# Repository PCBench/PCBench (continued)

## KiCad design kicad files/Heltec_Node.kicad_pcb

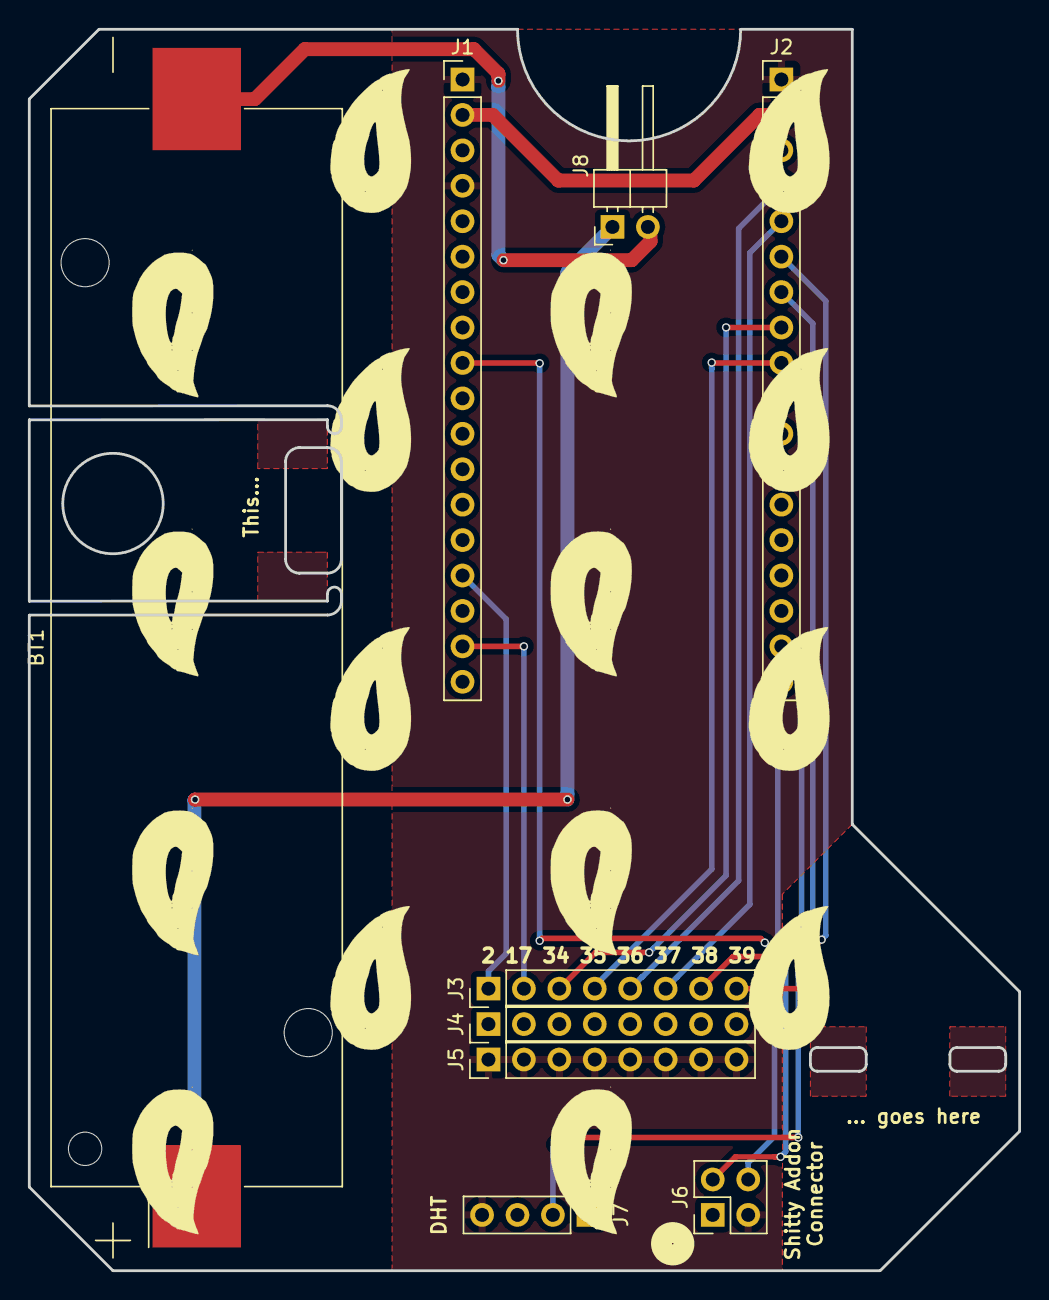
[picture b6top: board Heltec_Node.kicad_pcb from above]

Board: 2 copper layers, 71.0 x 89.0 mm, 9 parts (0 on the bottom side), 16 nets.

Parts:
BT1: Battery_Cell; Keystone_1042_1x18650
J1, J2: Conn_01x18_Female; Socket_Strip_Straight_1x18_Pitch2.54mm
J3, J4, J5: Conn_01x08; Pin_Header_Straight_1x08_Pitch2.54mm
J6: Conn_02x02_Top_Bottom; Pin_Header_Straight_2x02_Pitch2.54mm
J7: Conn_01x04; Pin_Header_Straight_1x04_Pitch2.54mm
J8: Conn_01x02; Pin_Header_Angled_1x02_Pitch2.54mm

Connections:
2: J1.15, J3.1
17: J1.17, J3.2
34: J2.8, J3.3
35: J2.9, J3.4
36: J2.4, J3.5
37: J2.5, J3.6
38: J2.6, J3.7
39: J2.7, J3.8
+3V3: J1.3, J2.3, J4.1, J4.2, J4.3, J4.4, J4.5, J4.6, J4.7, J4.8, J6.1, J7.1
+5V: J1.2, J2.2
DHT_D: J2.17, J7.2
GND: J1.1, J1.4, J2.1, J5.1, J5.2, J5.3, J5.4, J5.5, J5.6, J5.7, J5.8, J6.3, J7.4
unnamed: BT1.1, J8.1
unnamed: BT1.2, J8.2
SCL: J1.9, J6.4
SDA: J2.18, J6.2

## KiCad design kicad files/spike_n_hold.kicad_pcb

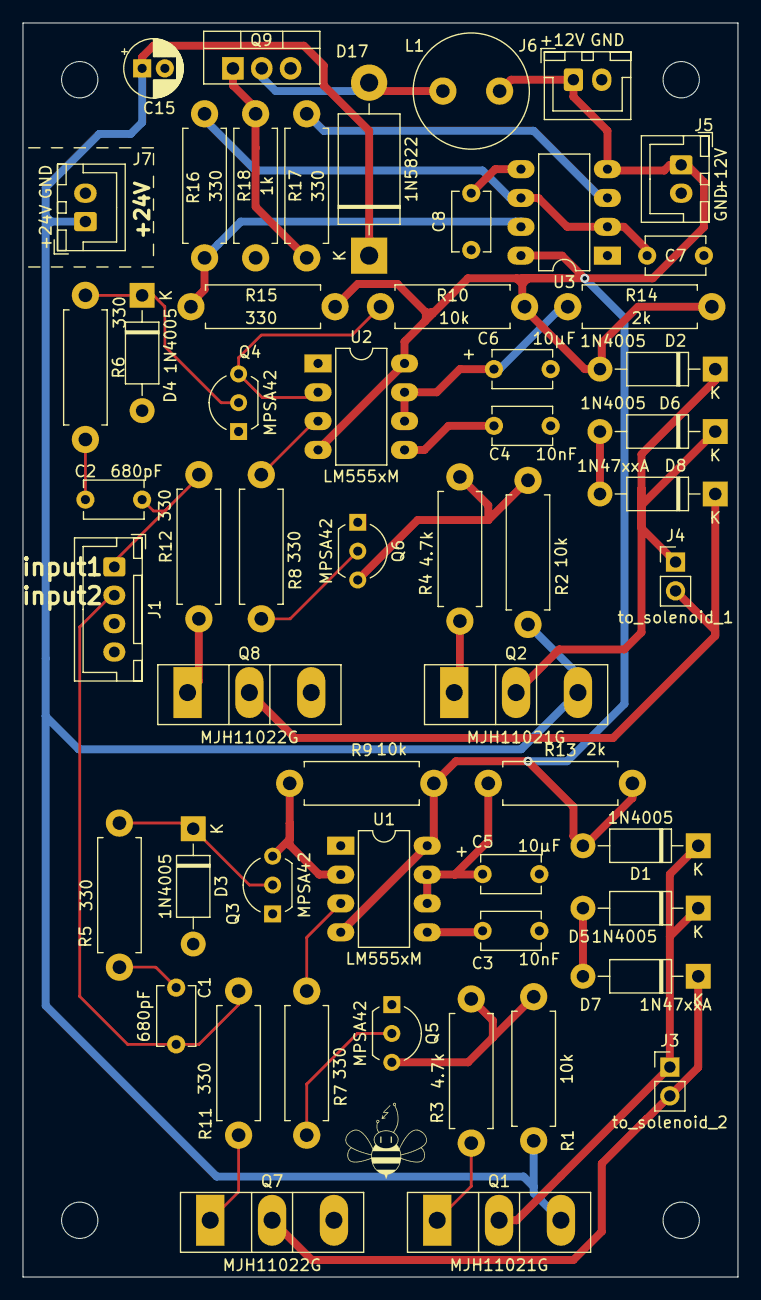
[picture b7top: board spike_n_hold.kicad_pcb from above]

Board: 2 copper layers, 63.0 x 110.5 mm, 59 parts (0 on the bottom side), 37 nets.

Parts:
C1, C2: 680pF; C_Disc_D5.1mm_W3.2mm_P5.00mm
C3, C4, C7, C8: 10nF; C_Disc_D5.1mm_W3.2mm_P5.00mm
C5, C6: 10µF; C_Disc_D5.1mm_W3.2mm_P5.00mm
C15: 22µF; CP_Radial_D5.0mm_P2.00mm
D1, D2, D3, D4, D5, D6: 1N4005; D_DO-41_SOD81_P10.16mm_Horizontal
D7, D8: 1N47xxA; D_DO-41_SOD81_P10.16mm_Horizontal
D17: 1N5822; D_DO-201AD_P15.24mm_Horizontal
H1, H2, H3, H4: MountingHole; MountingHole_3.2mm_M3
J1: Conn_01x04_Female; JST_XH_B4B-XH-A_1x04_P2.50mm_Vertical
J3: to_solenoid_2; PinHeader_1x02_P2.54mm_Vertical
J4: to_solenoid_1; PinHeader_1x02_P2.54mm_Vertical
J5, J6, J7: Conn_01x02; JST_XH_B2B-XH-A_1x02_P2.50mm_Vertical
L1: 33µH; L_Radial_D10.0mm_P5.00mm_Neosid_SD12_style3
Q1, Q2: MJH11021G; TO-247-3_Vertical
Q3, Q4, Q5, Q6: MPSA42; TO-92L_Inline_Wide
Q7, Q8: MJH11022G; TO-247-3_Vertical
Q9: IRFZ24NPBF; TO-220-3_Vertical
R1, R2, R9, R10: 10k; R_Axial_DIN0411_L9.9mm_D3.6mm_P12.70mm_Horizontal
R3, R4: 4.7k; R_Axial_DIN0411_L9.9mm_D3.6mm_P12.70mm_Horizontal
R5, R6, R7, R8, R11, R12, R15, R16, R17: 330; R_Axial_DIN0411_L9.9mm_D3.6mm_P12.70mm_Horizontal
R13, R14: 2k; R_Axial_DIN0411_L9.9mm_D3.6mm_P12.70mm_Horizontal
R18: 1k; R_Axial_DIN0411_L9.9mm_D3.6mm_P12.70mm_Horizontal
U1, U2, U3: LM555xM; DIP-8_W7.62mm_LongPads

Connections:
+12V: D1.2, D2.2, J5.1, J6.1, L1.1, R9.2, R10.2, R13.2, R14.2, R15.1, U1.4, U1.8, U2.4, U2.8, U3.4, U3.8
+24V: C15.1, D17.1, J7.1, Q1.3, Q2.3, R1.1, R2.1
GND: C3.1, C4.1, C5.2, C6.2, C7.1, C8.1, C15.2, D3.2, D4.2, J1.4, J5.2, J6.2, J7.2, Q3.1, Q4.1, Q5.1, Q6.1, Q7.3, Q8.3, Q9.3, R18.2, U1.1, U2.1, U3.1
unnamed: C1.1, R5.2
unnamed: C2.1, R6.2
unnamed: C3.2, U1.5
unnamed: C4.2, U2.5
unnamed: C5.1, R13.1, U1.6, U1.7
unnamed: C6.1, R14.1, U2.6, U2.7
unnamed: C7.2, R16.1, U3.2, U3.6
unnamed: C8.2, U3.5
unnamed: D1.1, D5.1, J3.1, Q1.2
unnamed: D2.1, D6.1, J4.1, Q2.2
unnamed: D3.1, Q3.2, R5.1
unnamed: D4.1, Q4.2, R6.1
unnamed: D5.2, D7.2
unnamed: D6.2, D8.2
unnamed: D7.1, J3.2, Q7.2
unnamed: D8.1, J4.2, Q8.2
unnamed: D17.2, L1.2, Q9.2
unnamed: Q1.1, R3.2
unnamed: Q2.1, R4.2
unnamed: Q3.3, R9.1, U1.2
unnamed: Q4.3, R10.1, U2.2
unnamed: Q5.2, R7.1
unnamed: Q5.3, R1.2, R3.1
unnamed: Q6.2, R8.1
unnamed: Q6.3, R2.2, R4.1
unnamed: Q7.1, R11.1
unnamed: Q8.1, R12.1
unnamed: Q9.1, R17.2, R18.1
unnamed: R15.2, R16.2, U3.7
unnamed: R17.1, U3.3
input_trigger1: C2.2, J1.1, R12.2
input_trigger2: C1.2, J1.2, R11.2
timed_trigger1: R8.2, U2.3
timed_trigger2: R7.2, U1.3
